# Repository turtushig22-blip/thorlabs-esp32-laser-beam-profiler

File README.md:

# Automated High-Density Knife-Edge Laser Beam Profiler

**This repository documents an undergraduate experimental physics project focused on measuring laser beam waists using the knife-edge method. The project involved developing an automated measurement setup using Thorlabs motion-control hardware, an ESP32-based data acquisition system, custom electronics, and Python scripts for data processing and analysis. We tested the setup using a diode laser and a HeNe laser and investigated different approaches to extracting beam parameters from the measured power profiles. The repository contains the experimental data, hardware designs, acquisition software, analysis scripts, and project documentation.**.

---

## Repository Organization & Environments

> **Note on Project Code & Hardware Files:**
> * **Python & Analysis Tools:** To inspect the complete runtime environment and execution pipeline, please see the [`code/`](#) folder (where `master_python.py`, fitting routines, and analysis tools are stored).
> * **Hardware & PCB Design:** For the custom printed circuit board schematics, layout, and fabrication gerbers, please see the [`KiCad/`](#) directory.

---
 <br>
Figure 1. Photograph of the HeNe laser beam propagating through the experimental optical arrangement used for knife-edge beam profiling, viewed from an angle facing the incoming beam.

## Overview

Characterizing laser beam characteristics, beam waists (w<sub>0</sub>), and propagation quality ($M^2$) at micron-level scales requires dense spatial sampling and low-noise instrumentation. Manual knife-edge profiling suffers from coarse positioning, slow acquisition rates, and human parallax errors.

This project delivers an automated knife-edge laser beam profiler:
1. **Sub-Micron Actuation:** A **Thorlabs NRT100** linear translation stage driven by a **TST001** stepper motor controller via a **TCH002** hub, stepping a precision commercial razor blade in increments as fine as **$0.5\mu\text{m}$** (with step support down to $0.1\mu\text{m}$).
2. **Custom Signal Processing & Embedded DAQ:** Optical power is acquired via a **Thorlabs PM100A** optical power meter. The analog output is filtered through a hardware 1st-order RC low-pass filter ($f_c \approx 15.92\,\text{Hz}$), digitized by a 16-bit **ADS1115** ADC, and managed by an **ESP32** microcontroller running custom firmware with real-time S-curve rendering on an **ILI9341** 2.8" SPI TFT display.
3. **Automated Host Organization:** A Python-based host (`master_python.py`) synchronizes stage translation, introduces settling dwells ($0.5\text{s}$), acquires dark-background-corrected voltages, performs real-time encoder verification, and logs structured scan datasets.
4. **Statistical & Optical Modeling:** Implements non-linear error function ($\mathrm{erfc}$) S-curve fits, rolling-median $3\sigma$ outlier rejection, adaptive-window derivative comparisons (Power distribution S-curve fit vs. Intensity Gaussian curve fit), and Tikhonov-regularized non-linear least-squares propagation modeling to account for millimeter-ruler positioning uncertainty ($\sigma_z \approx 0.289\text{mm}$).

---

## Experimental Setup

```
 Laser Source            Keplerian Expander                Focusing Lens         Knife-Edge Plane          Power Sensor
[ HeNe / Diode ] ---> [ L1 (f=75mm) + L2 (f=160mm) ] ---> [ L3 (f=75mm) ] ---> [ Razor on NRT100 ] ---> [ Thorlabs PM100A ]
                            (M_exp ≈ 2.13x)                                       (0.5 µm steps)                |
                                                                                                                v
                                                                                                     Analog Out (0.0-2.0 V)
                                                                                                                |
                                                                                                                v
                                                                                                     [ RC Low-Pass Filter ]
                                                                                                        (fc ≈ 15.92 Hz)
                                                                                                                |
                                                                                                                v
                                                                                                     [ ADS1115 16-bit ADC ]
                                                                                                                |
                                                                                                                v
                                             [ Host PC / master_python.py ] <==== USB Serial <==== [ ESP32 Microcontroller ] ====> [ ILI9341 2.8" TFT ]
                                                           |                                                                        (Real-Time S-Curve)
                                                           v (FTDI D2XX / pylablib)
                                              [ Thorlabs TST001 / NRT100 ]
```
 
 <br>
Figure 2. Schematic optical train. L1 (f = 7.5 cm) and L2 (f = 16.0 cm) form a Keplerian beam expander (magnification ≈ 2.13); L3 (f = 7.5 cm) focuses the beam to the knife-edge plane.
### Optical Specifications
* **Lasers Used:**
  * HeNe Laser: $\lambda = 632.8\text{nm}$, $TEM_{00}$ fundamental mode.
  * TeachSpin DLI-A Diode Laser: Nominal $780\text{nm}$, experimentally calibrated at $\lambda = 780.9\text{nm}$ (instrument-limited linewidth $\Delta\lambda \lesssim 3\text{nm}$).
* **Expander:** Keplerian telescope composed of plano-convex lenses $L_1$ ($f_1 = 7.5\text{cm}$) and $L_2$ ($f_2 = 16.0\text{cm}$) giving a magnification $M_\text{exp} of \approx 2.13$.
* **Focusing Optic:** Plano-convex singlet $L_3$ ($f_3 = 7.5\text{cm}$), establishing a tight waist at the knife-edge plane.
* **Actuation Stage:** Thorlabs NRT100 with internal optical encoder ($25{,}600\text{microsteps/mm}$), scanning $1000$ steps ($0.5\text{mm}$ travel) per axial $z$-position.

---

## Custom PCB (`KiCad/`)

The analog signal conditioning and digitization circuit is designed as a dedicated PCB in KiCad 9.0, located in the [`KiCad/`](#) folder:

* **Schematic & Layout:** [`KiCad/BeamWaist.kicad_sch`](#) and [`KiCad/BeamWaist.kicad_pcb`](#)
* **Fabrication Files:** Production Gerber archives in [`KiCad/BeamWaistGerbers/`](#)
 <br>
Figure 3. Circuit diagram of the laser power measurement acquisition electronics, showing the RC low-pass filter, ADS1115 16-bit ADC, ESP32 microcontroller, and TFT display. The PM100A analog output
serves as the input signal, while the 100 nF capacitor between A0 and GND provides additional input filtering. The USB-serial connection and host-side data acquisition system are omitted for clarity.

---

## Software Suite & Scripts (`code/`)

All data acquisition, reduction, fitting, and visualization code is housed in [`code/`](#). Below is a complete reference of the primary scripts:

### 1. `master_python.py` (Master DAQ Host Controller)
* **Role:** Primary coordinator interfacing the experiment.
* **Functionality:**
  * Establishes FTDI communication (`libftd2xx.dylib`, `pylablib`) to command the Thorlabs TST001 controller.
  * Handles stage motion, waiting routines, and dwell settling times ($0.5\text{s}$).
  * Communicates with ESP32 via USB-Serial (`pyserial`).
  * Executes automated dark-background measurement ($N_\text{bg} = 100$ samples) and subtraction.
  * Performs active closed-loop encoder monitoring (flags position discrepancy if error exceeds $2\mu\text{m}$).
  * Auto-increments and saves run metadata to CSV files (`beamscan_run_NNN.csv`).

### 2. `beam_waist_fit.py` (Caustic Propagation & Ruler Uncertainty Fitter)
* **Role:** Evaluates beam waist radius $w_0$, waist axial position $z_0$, and beam quality factor $M^2$.
* **Functionality:**
  * Solves the Gaussian beam propagation equation:
    $$w^2(z) = w_0^2 + \left[\frac{M^2 \lambda}{\pi w_0}(z - z_0)\right]^2$$
  * Features a Tikhonov-regularized dual-residual objective:
    $$\mathbf{r}(\boldsymbol{\theta}, \boldsymbol{\delta z}) = \begin{pmatrix} \frac{w^2(z_i + \delta z_i; \boldsymbol{\theta}) - w_i^2}{\sigma_{w^2, i}} \\ \frac{\delta z_i}{\sigma_z} \end{pmatrix}$$
    where $\sigma_z = \frac{0.5\text{mm}}{\sqrt{3}} \approx 0.289\text{mm}$ captures reading uncertainty on the millimeter bench ruler.
  * Compares unregularized ("$z$ exact") vs. regularized ("$z$ uncertain") models, producing comparative plots and nuisance shift diagnostics ($\delta z_i$).

### 3. `dual_fit_comparison.py` (Method A vs. Method B Benchmark)
* **Role:** Systematic cross-validation of beam extraction techniques:
  * **Method A:** Non-linear least-squares fit directly to the integrated power S-curve ($\mathrm{erfc}$ model).
  * **Method B:** Numerical differentiation of the S-curve ($\mathrm{d}P/\mathrm{d}x$) followed by a Gaussian fit ($\sigma = w/2$).
* **Adaptive Smoothing Analysis:** Demonstrates how static rolling averages ($N = 100$) artifically broaden derivative peaks near tight waists (up to $+55\%$ on HeNe and $+129\%$ on Diode), and implements an adaptive window:
  $$N_\text{adaptive} = \max\left(N_\text{min}, \mathrm{round}\left(\frac{\alpha w_A}{\Delta x_\text{step}}\right)\right)$$
  showing why direct $\mathrm{erfc}$ fitting (Method A) is superior.

### 4. `erfc_fitter.py` & `erfc_fitter_hene.py` (Single-Run S-Curve Extractors)
* **Role:** Detailed profiling and analysis of individual scan CSV files.
* **Features:**
  * $3\sigma$ outlier filtering against a 15-point rolling median.
  * Automatic deterministic initial parameter guessing ($y_0, P_0, x_0, w_0$).
  * Non-linear Levenberg-Marquardt / Trust-Region fitting using `scipy.optimize.curve_fit`.
  * Extraction of parameter covariance $\sigma_{w^2} = 2w\sigma_w$.

### 5. `plot_spectrometer.py` (Diode Laser Spectral Analysis)
* **Role:** Ingests raw spectral output (`spectrometer_data.csv`) from the Ocean Optics / USB fiber spectrometer.
* **Features:**
  * Full spectrum survey ($750\text{--}820\,\text{nm}$) and high-resolution zoomed window ($778\text{--}786\text{nm}$).
  * Gaussian fitting demonstrating center emission at $\lambda = 780.9\text{nm}$.
  * Resolves instrument-limited FWHM ($\Delta\lambda \lesssim 3\text{nm}$) consistent with single-longitudinal-mode operation.
---

## Summary of Experimental Results
From the comprehensive <a href="Beam_Waist_Report.pdf"> lab report</a>:

| Parameter | HeNe Laser ($\lambda = 632.8\text{nm}$) | Diode Laser ($\lambda = 780.9\text{nm}$) |
| :--- | :---: | :---: |
| **Beam Waist ($w_0$)** | **$30.80\mu\text{m}$** | **$9.81\mu\text{m}$** |
| **Waist Location ($z_0$)** | $542.4\text{mm}$ | $333.4\text{mm}$ |
| **Beam Quality Factor ($M^2$)** | **$1.13$** (Near-ideal TEM$_{00}$) | **$1.00^\dagger$** (Astigmatic limit) |
| **Rayleigh Range ($z_R$)** | $\approx 4.16\text{mm}$ | $\approx 0.39\text{mm}$ |
| **Nominal Reduced $\chi^2$ ($z$-exact)** | $314.7$ | $12{,}886$ |
| **Nominal Reduced $\chi^2$ ($z$-uncertain)** | **$7.65$** | **$4.14$** |

$^\dagger$ *Note on Diode $`M^2`$: The optimization parameter converged to its physical lower bound ($`M^2`$ = 1.0), resulting from semiconductor laser astigmatism (asymmetric fast vs. slow divergence axes creating shifted caustics across orthogonal transverse planes).*

---

## Getting Started & Environment Setup

### 1. Prerequisites
* **Operating System:** macOS (Apple Silicon / Intel) or Linux.
* **Python:** 3.10 or higher.
* **Hardware Drivers:** FTDI D2XX driver installed (`libftd2xx.dylib` on macOS or `libftd2xx.so` on Linux).

### 2. Python Environment Setup
Navigate to the project root and create a virtual environment:

```bash
# Clone repository
git clone https://github.com
cd thorlabs-esp32-laser-beam-profiler

# Set up Python virtual environment
python3 -m venv .venv
source .venv/bin/activate

# Install required dependencies
pip install numpy scipy matplotlib pandas pyserial pylablib
```

### 3. ESP32 Firmware Flashing
1. Open [`code/esp32_script.cpp`](#) in Arduino IDE.
2. Ensure the following libraries are installed:
   * `Adafruit_GFX`
   * `Adafruit_ILI9341`
   * `Adafruit_ADS1X15`
3. Connect the ESP32 via USB and flash the board (Note that the baud rate has to be `115200`).

### 4. Running a Data Acquisition Run
Connect the Thorlabs TST001 controller and ESP32 board, verify serial ports, and run:

```bash
python code/master_python.py
```

### 5. Running Beam Fitting & Analysis

```bash
# Run caustic propagation fitting (with axial ruler uncertainty propagation)
python code/beam_waist_fit.py

# Compare Method A (ERFC) vs Method B (Adaptive Derivative)
python code/dual_fit_comparison.py

# Plot spectrometer spectral emission
python code/plot_spectrometer.py
```

---

## Repository Structure

```
.
├── README.md                      # Comprehensive project documentation
├── BeamWaist_report.tex           # Complete LaTeX report
├── code/                          # Unified Python codebase
│   ├── master_python.py           # Automated DAQ ecosystem (Thorlabs + ESP32)
│   ├── beam_waist_fit.py          # Caustic propagation fitting & regularized LSQ
│   ├── dual_fit_comparison.py     # Method A (Power curve erfc fit) vs Method B (Intensity curve Gaussian fit) comparison
│   ├── erfc_fitter.py             # Single-scan S-curve filter & erfc fitting (Diode)
│   ├── erfc_fitter_hene.py        # Single-scan S-curve filter & erfc fitting (HeNe)
│   ├── plot_spectrometer.py       # Diode spectrometer analysis & Gaussian peak fitting
│   ├── esp32_script.cpp           # ESP32 firmware (ADC oversampling & TFT S-curve display)

├── KiCad/                         # Hardware electronics & custom DAQ PCB
│   ├── BeamWaist.kicad_sch        # Circuit schematic (ADS1115, RC filter, ESP32)
│   ├── BeamWaist.kicad_pcb        # PCB board layout & routing
│   └── Gerbers/                   # Production-ready Gerber and drill files

├── BeamWaistData/                 # Raw experimental scan datasets (CSV)
│   ├── beamscan_run_014.csv
│   └── ...

└── figures/                       # Rendered plots and optical diagrams
    ├── dual_fit_hene.png          # HeNe dual-method fitting comparison
    ├── dual_fit_diode.png         # Diode dual-method fitting comparison
    └── spectrometer_plot.png      # Measured diode laser spectrum
```

---

## Authors & Context

* **Author:** Turtushig Dashjav 
* **Supervisor:** Eric Wells, Ph.D.
* **Affiliation:** Department of Physics, Augustana University, Sioux Falls, SD, USA

---

## References
* **Key Literature:**
  * B. E. A. Saleh and M. C. Teich, Fundamentals of Photonics (Wiley Series in Pure and Applied
Optics), 3rd. Hoboken, NJ, USA: John Wiley & Sons, 2019.
  * International Organization for Standardization, “Lasers and laser-related equipment — test methods
for laser beam widths, divergence angles and beam propagation ratios — part 1: Stigmatic and simple
astigmatic beams,” International Organization for Standardization, Geneva, Switzerland, Standard
ISO 11146-1:2021, 2021.
  * W. Plass, R. Maestle, K. Wittig, A. Voss, and A. Giesen, “High-resolution knife-edge laser beam
profiling,” Optics Communications, vol. 134, no. 1–6, pp. 21–24, 1997.
  * W. H. Press, S. A. Teukolsky, W. T. Vetterling, and B. P. Flannery, Numerical Recipes: The Art of
Scientific Computing, 3rd ed. Cambridge University Press, 2007.
  * Photonics Media, Laser wavelength meter, https : / / www . photonics . com / Products / Laser -
Wavelength-Meter/pr22699, Accessed: October 12, 2026.
  * Vernier Science Education, Go direct® spectrovis® plus spectrophotometer specifications, https://www.
vernier.com/product/go- direct- spectrovis- plus- spectrophotometer/, Accessed: October
12, 2026, 2026.
  * W. Plass, R. Maestle, K. Wittig, A. Voss, and A. Giesen, The irradiance profile of the astigmatic
beam emitting from the tube with spot profile at different positions, https://www.researchgate.
net/figure/The-irradiance-profile-of-the-astigmatic-beam-emitting-from-tube-with-
spot-profile-at_fig6_230615553, Accessed: October 18, 2026, 1996.

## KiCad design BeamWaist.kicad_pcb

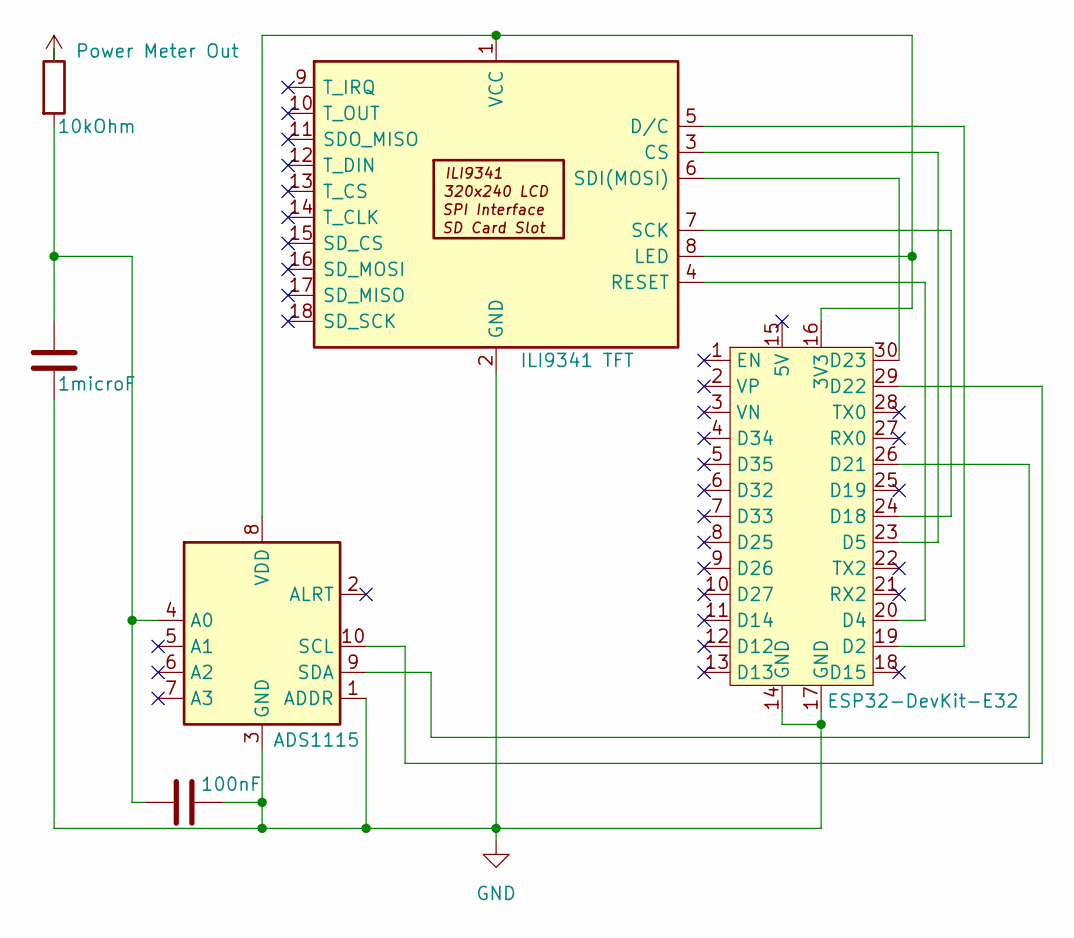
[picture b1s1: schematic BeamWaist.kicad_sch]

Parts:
C1: 100nF; C_Disc_D7.0mm_W2.5mm_P5.00mm
C2: 1microF; CP_Radial_D5.0mm_P2.50mm
R1: 10kOhm; R_Axial_DIN0207_L6.3mm_D2.5mm_P7.62mm_Horizontal
U1: ADS1115
U2: ESP32-DevKit-E32; ESP32-WROOM-E32
U3: ILI9341 TFT; ILI9341

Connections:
GND: C1.2, C2.2, U1.1 (ADDR), U1.3 (GND), U2.14 (GND), U2.17 (GND), U3.2 (GND)
unnamed: C1.1, C2.1, R1.2, U1.4 (A0)
unnamed: U1.10 (SCL), U2.29 (D22)
unnamed: U1.9 (SDA), U2.26 (D21)
unnamed: U1.8 (VDD), U2.16 (3V3), U3.1 (VCC), U3.8 (LED)
unnamed: U2.19 (D2), U3.5 (D/C)
unnamed: U2.20 (D4), U3.4 (RESET)
unnamed: U2.23 (D5), U3.3 (CS)
unnamed: U2.24 (D18), U3.7 (SCK)
unnamed: U2.30 (D23), U3.6 (SDI(MOSI))
VCC: R1.1

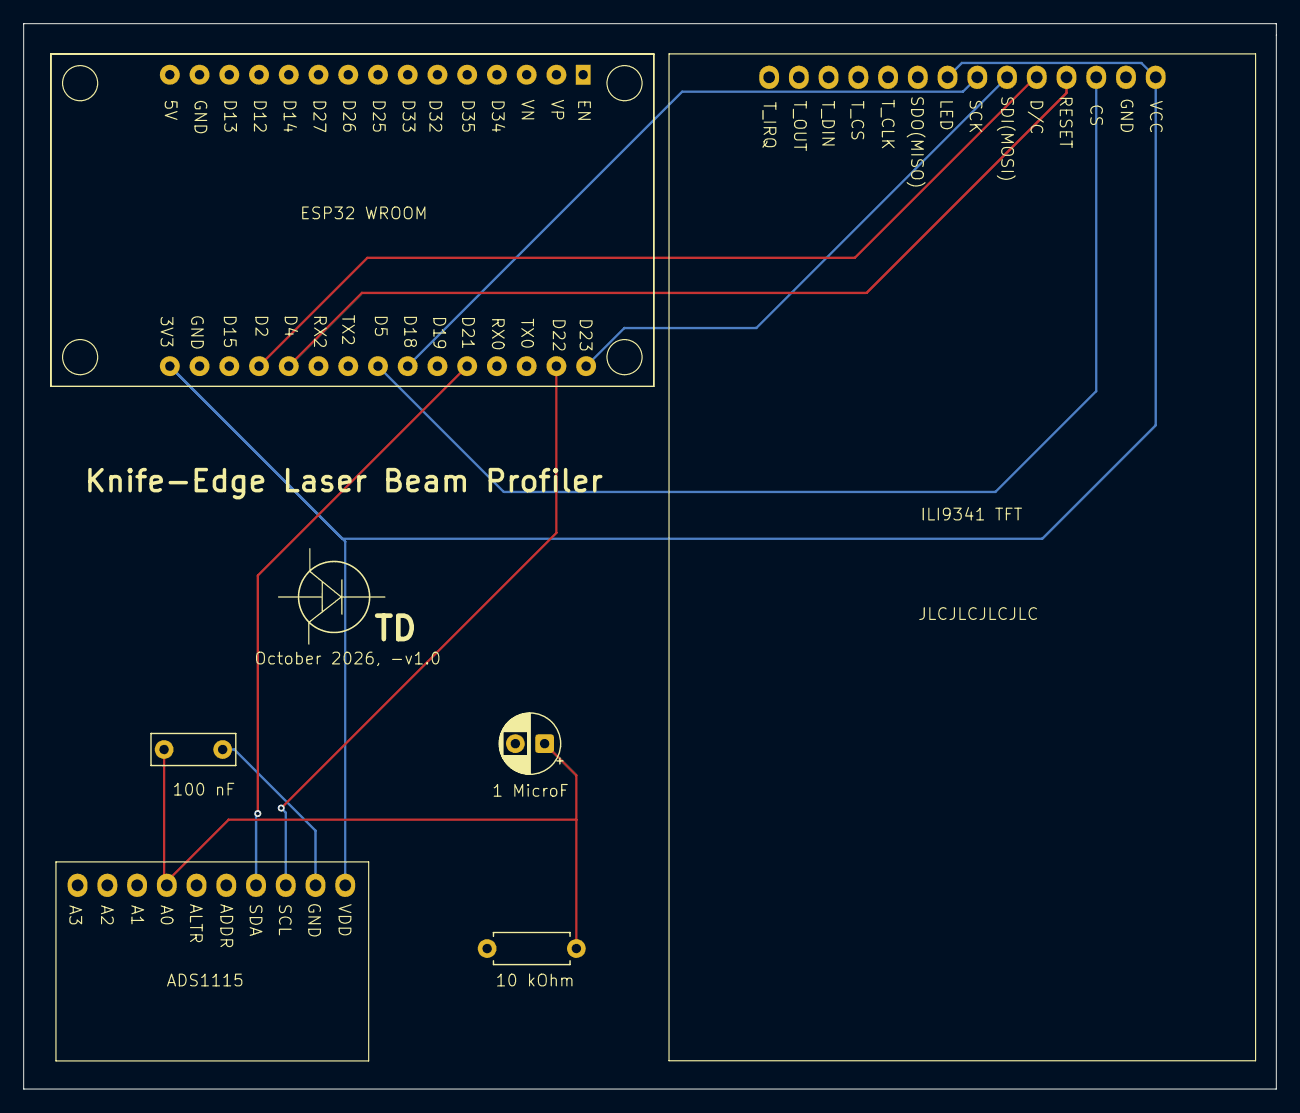
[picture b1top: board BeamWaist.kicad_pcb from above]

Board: 4 copper layers, 107.0 x 91.0 mm, 6 parts (0 on the bottom side), 10 nets.

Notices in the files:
README.md:
License: MIT
